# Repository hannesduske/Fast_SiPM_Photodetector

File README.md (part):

# Fast SiPM Photodetector

This photodetector is built around the fast output of the onsemi MicroFC-30035 silicon photomultiplier (SiPM).
It combines an adjustable sensor-bias supply, an integrated low-noise amplifier, and an analog temperature sensor for external temperature control.
The detector can measure nanosecond-scale events and achieves single-photon resolution.

<div align="center">
<table style="border: none;">
  <tr>
    <td style="text-align:center">
      <br>
    </td>
    <td style="text-align:center">
      <br>
    </td>
  </tr>
</table>
</div>

## Table of Contents

- [1. Technical Specification](#1-technical-specification)
  - [1.1 Key Features](#11-key-features)
  - [1.2 Design Specification](#12-design-specification)
  - [1.3 The MicroFC-30035 SiPM](#13-the-microfc-30035-sipm)
- [2. Circuit Design](#2-circuit-design)
  - [2.1 Overview](#21-overview)
  - [2.2 Input Protection](#22-input-protection)
  - [2.3 HV Power Supply](#23-hv-power-supply)
  - [2.4 LV Power Supply](#24-lv-power-supply)
  - [2.5 Photodetector](#25-photodetector)
  - [2.6 Amplifier](#26-amplifier)
  - [2.7 Temperature Sensor](#27-temperature-sensor)
- [3. PCB Layout](#3-pcb-layout)
  - [3.1 Physical Dimensions](#31-physical-dimensions)
  - [3.2 Peripheral Components](#32-peripheral-components)
  - [3.3 Assembled Detector Boards](#33-assembled-detector-boards)
- [4. Detector Performance](#4-detector-performance)
  - [4.1 Output Noise Performance](#41-output-noise-performance)
  - [4.2 Thermal Performance, Active Cooling and Dark Count](#42-thermal-performance-active-cooling-and-dark-count)
  - [4.3 Single Photon Detection](#43-single-photon-detection)
  - [4.4 Observing Nanosecond Light Pulses](#44-observing-nanosecond-light-pulses)
- [5. References](#5-references)
  - [5.1 Datasheets of Main Components](#51-datasheets-of-main-components)
  - [5.2 Reference Documents](#52-reference-documents)
  - [5.3 Design Tools](#53-design-tools)

## 1. Technical Specification

### 1.1 Key Features

This detector board is built around the [MicroFC-30035](https://www.onsemi.com/pub/Collateral/MICROC-SERIES-D.PDF) SiPM and uses its fast output for readout.
The fast output is amplified by a [GALI-S66+](https://www.minicircuits.com/pdfs/GALI-S66+.pdf) RF amplifier.
The SiPM bias voltage is generated by an integrated [LT8365](https://www.analog.com/media/en/technical-documentation/data-sheets/lt8365.pdf) boost converter followed by an adjustable low-noise LDO and can be adjusted from $23.8\ \mathrm{V}$ to $29.1\ \mathrm{V}$.
Separate high-voltage and low-voltage power rails are created on board from a single input voltage.

An [MCP9700A](https://ww1.microchip.com/downloads/en/devicedoc/20001942g.pdf) analog temperature sensor is also included on the board to enable external temperature control.

### 1.2 Design Specification

<div align="center">

| Parameter | Value |
|-|-|
| Input Voltage | $7.5\ \mathrm{V}$ to $24\ \mathrm{V}$ |
| SiPM | onsemi MicroFC-30035 |
| SiPM Bias Adjustment | $23.8\ \mathrm{V}$ to $29.1\ \mathrm{V}$ |
| Amplifier | GALI-S66+ |
| Fast-Output Amplification | $+20.3\ \mathrm{dB}$ @ $1\ \mathrm{GHz}$ (typ.) |
| Amplifier Output | Voltage readout, $50\ \Omega$ matched |
| Temperature Sensor | MCP9700A with analog output |
| Input Protection | Reverse voltage protection <br> Short-circuit protection |

</div>

> ℹ️ The lower input voltage limit is set by the undervoltage shutdown of the high-voltage supply. Refer to [2.3](#23-hv-power-supply).

> ℹ️ The MicroFC-30035 datasheet specifies a breakdown voltage of $24.2\ \mathrm{V}$ to $24.7\ \mathrm{V}$ and a recommended overvoltage of $1\ \mathrm{V}$ to $5\ \mathrm{V}$.
> The upper bias limit of $29.1\ \mathrm{V}$ corresponds to an overvoltage of $4.4\ \mathrm{V}$ to $4.9\ \mathrm{V}$.
> The lower bias limit of $23.8\ \mathrm{V}$ is below the breakdown voltage.

### 1.3 The MicroFC-30035 SiPM

The MicroFC-30035 was chosen for this project because of its unique fast output.

The fast output of the MicroFC-30035 has a rise time of $600\ \mathrm{ps}$ and is well suited for timing experiments and for observing fast transients.
The electronic readout and amplification of the fast output are also very simple.
Because it is a direct voltage output, it can be amplified with standard wideband RF amplifiers.

The MicroFC-30035 is sensitive to blue light and has its peak sensitivity at $420\ \mathrm{nm}$.

<div align="center">
  <br>
  <p>Photon Detection Efficiency (PDE) of the MicroFC-30035 (<a href="https://www.onsemi.com/pub/Collateral/MICROC-SERIES-D.PDF">Datasheet p. 7</a>)</p>
</div>

## 2. Circuit Design

### 2.1 Overview

<div align="center">
  <br>
</div>

The complete schematic is available [here](01_Docs/02_Schematic/sipm_photo_detector_v0_2.pdf) as a PDF.

The MicroFC-30035 is the main component of this detector board, and the entire circuit is designed to maximize its performance through:
- heavy filtering on the SiPM and amplifier supply rails
- $50\ \Omega$ matched transmission lines and high-frequency RF components
- EMI shielding

### 2.2 Input Protection

<div align="center">
  <br>
</div>

The detector is protected against reverse input voltages through MOSFET $\mathrm{Q1}$.
Additionally, the input stage includes the SMD fuse $\mathrm{F1}$ for short-circuit protection.
The detector can be physically turned on and off by switch $\mathrm{SW1}$.

There are no power indicator LEDs on the board to avoid interference with the sensor.

### 2.3 HV Power Supply

<div align="center">
  <br>
</div>

The high-voltage rail is exclusively used to supply the SiPM bias voltage.
It is generated with the LT8365 boost converter $\mathrm{IC1}$ and is set to $30.4\ \mathrm{V}$ by the feedback resistors $\mathrm{R5}$ and $\mathrm{R6}$.
The converter input is filtered by the ferrite bead $\mathrm{FB1}$ and the surrounding capacitors.

The high-voltage regulator shuts down when the input voltage falls below $7.5\ \mathrm{V}$.
This undervoltage threshold is set by the enable network formed by $\mathrm{R7}$ and $\mathrm{R8}$.

### 2.4 LV Power Supply

<div align="center">
  <br>
</div>

The low-voltage supply uses the LMR51606 buck converter $\mathrm{IC2}$ to generate a fixed $6.6\ \mathrm{V}$ rail.
The output voltage is set by the feedback network formed by $\mathrm{R11}$ and $\mathrm{R12}$.
The converter input is filtered by the ferrite bead $\mathrm{FB3}$ and the surrounding capacitors.

The enable network formed by $\mathrm{R9}$ and $\mathrm{R10}$ monitors the high-voltage rail and turns the converter on at approximately $23.3\ \mathrm{V}$.
The low-voltage rail therefore only turns on once the high-voltage supply has stabilized.

The output voltage is set as high as possible for the minimum input voltage of $7.5\ \mathrm{V}$ to improve amplifier performance.

### 2.5 Photodetector

<div align="center">
  <br>
</div>

The HV supply rail is filtered with a capacitance multiplier stage that is built with the Darlington transistor $\mathrm{Q2}$ to minimize supply ripple from the LT8365 converter.
The filtered voltage is then reduced further with the adjustable low-noise LDO $\mathrm{IC4}$ to precisely set the SiPM bias voltage.
The bias voltage is continuously adjustable from $23.8\ \mathrm{V}$ to $29.1\ \mathrm{V}$ with the on-board potentiometer $\mathrm{RV1}$.

It is possible to override the on-board potentiometer with an external one for use cases where the detector is integrated into a larger assembly.
To keep the circuit simple, the external potentiometer is connected in parallel with $\mathrm{RV1}$.
Therefore, when using an external potentiometer, the on-board potentiometer must be set to its **highest resistance** to produce the **minimum bias voltage**.
The output voltage can then be adjusted with a high-resistance external potentiometer connected between `BIAS_ADJ` (CONN2 pin 1) and `GND` (CONN2 pin 2).
An external potentiometer with a resistance of at least $100\ \mathrm{k}\Omega$ is recommended to preserve the full voltage adjustment range.

> ℹ️ The MicroFC application note [AND9782-D](https://www.onsemi.com/pub/Collateral/AND9782-D.PDF) recommends using a negative bias on the anode, with the cathode at $0\ \mathrm{V}$, for the best fast-output timing performance of this SiPM.
> Currently, a positive supply rail is used, but the LT8365 can be configured to generate a negative voltage instead.
> In this case, the adjustable LDO would need to be replaced with a negative-voltage version.

### 2.6 Amplifier

<div align="center">
  <br>
</div>

The fast-output signal is amplified by the GALI-S66+ RF amplifier $\mathrm{U1}$.
This stage is critical to detector performance and is laid out as a dedicated high-frequency signal path with an optional shielding can.
The high-frequency path uses $50\ \Omega$ transmission lines and high-quality C0G/NP0 capacitors for improved performance.
The amplifier's bias tee uses two RF inductors of different sizes, $\mathrm{L3}$ and $\mathrm{L4}$, for good performance over a wide frequency range.

A second capacitance multiplier stage with the Darlington transistor $\mathrm{Q3}$, similar to the one in the SiPM bias supply, is used to filter the amplifier supply voltage.

### 2.7 Temperature Sensor

<div align="center">
  <br>
</div>

The local $3.3\ \mathrm{V}$ LDO $\mathrm{U2}$ powers the MCP9700A temperature sensor $\mathrm{U3}$ from the low-voltage rail.
The MCP9700A outputs an analog voltage that changes linearly with the sensor temperature.
The temperature sensor output is filtered with the small capacitor $\mathrm{C26}$ and protected by the series resistor $\mathrm{R18}$ to prevent damage in case the output pin is accidentally shorted.

> ℹ️ The [MCP9700A datasheet](https://ww1.microchip.com/downloads/en/devicedoc/20001942g.pdf) specifies a typical output voltage of $500\ \mathrm{mV}$ at $T_A=0\ \mathrm{^\circ C}$ and a temperature coefficient of $T_C=10\ \mathrm{mV/^\circ C}$.
> The sensor temperature can therefore be calculated as $T_A=(U_{out} - 0.5\ \mathrm{V}) \cdot 100 \frac{\mathrm{^\circ C}}{\mathrm{V}}$.
> Refer to the MCP9700A datasheet for more information on sensor readout and accuracy.

> ℹ️ The temperature sensor is provided as an auxiliary feature to support an external temperature controller.
> The detector board does not include the controller's power electronics for the following reasons:
> - A linear controller is recommended over a switching controller to protect the sensitive detector circuit from switching noise.
> - Linear controllers dissipate significant power and generate heat.
> - This heat must be kept away from the SiPM. Otherwise, it would counteract the active cooling.
>
> For these reasons, the temperature controller is to be implemented externally.

## 3. PCB Layout

### 3.1 Physical Dimensions

The V0.2 PCB measures $60\ \mathrm{mm} \times 40\ \mathrm{mm}$ and has an M3 hole pattern of $50\ \mathrm{mm} \times 30\ \mathrm{mm}$.

The PCB is laid out around the central MicroFC-30035.
Care has been taken to keep switching signals away from the sensor and amplifier, and a four-layer PCB stackup has been chosen for better EMI performance.
Additionally, the amplifier stage is designed to fit inside a $10\ \mathrm{mm} \times 15\ \mathrm{mm}$ clip-on metal shielding can.

The center of the bottom layer of the PCB is intentionally kept free of components and THT holes to allow a $40\ \mathrm{mm} \times 40\ \mathrm{mm}$ thermoelectric cooler to be mounted directly below the sensor.

<div align="center">
  <br>
</div>

### 3.2 Peripheral Components

Below is a functional description of the main peripheral components of the PCB.

<div align="center">
<br>

| Reference | Description |
|-|-|
| SW1   | On/off switch. Switches the input voltage. |
| POT1  | Bias voltage adjustment. |
| SMA1  | Amplified fast output of the SiPM ($50\ \Omega$). |
| CONN1 | DC input. $7.5\ \mathrm{V}$ to $24\ \mathrm{V}$. Pin order: `V`, `G`. Mating plug: [PTSM 0,5/ 2-P-2,5](https://www.phoenixcontact.com/en-de/products/pcb-connector-ptsm-05-2-p-25-1778832). |
| CONN2 | External bias override and analog temperature output, each with its own ground pin. Pin order: `B` (`BIAS_ADJ`), `G`, `T` (`TEMP_OUT`), `G`. Mating plug: [PTSM 0,5/ 4-P-2,5](https://www.phoenixcontact.com/en-de/products/pcb-connector-ptsm-05-4-p-25-1778858). |
| FUSE1 | 0603 SMD fuse ($3\ \mathrm{A}$) for short-circuit protection. |
</div>

> ℹ️ The connectors on the board are the PTSM 0,5/ 2-HH-2,5-SMD R32 (CONN1) and PTSM 0,5/ 4-HH-2,5-SMD R32 (CONN2) headers.

### 3.3 Assembled Detector Boards

The front and back of the assembled Fast SiPM Photodetector V0.2 PCB are shown below.
Two boards were assembled for performance testing.

<div align="center">
  <br>
  <p>Front and back sides of the assembled Fast SiPM Photodetector V0.2 PCB.</p>
</div>

## 4. Detector Performance

### 4.1 Output Noise Performance

With the SiPM bias set to $24\ \mathrm{V}$, the measured output noise is $87.0\ \mathrm{\mu V RMS}$ over a bandwidth of $250\ \mathrm{MHz}$.
The dense baseline noise floor, approximately $0.8\ \mathrm{mV}$ peak-to-peak, remains constant across the bias adjustment range and across the input voltage range.
The trace also shows spikes at the LT8365 boost converter's switching frequency, with an amplitude of approximately $1.5\ \mathrm{mV}$ peak-to-peak.
As the input voltage increases, the spike frequency decreases and the measured total noise is reduced.

The main issue with these spikes is that they interfere with single-photon detection at bias voltages below $27\ \mathrm{V}$ because their amplitude is similar to that of single-photon events.
At bias voltages above $27\ \mathrm{V}$, the noise spikes can be distinguished cleanly from real detection events.

<div align="center">
<table style="border-collapse: collapse; border: none;">
  <tr>
    <td style="border: none; text-align: center;">
      <br>
      <p>Output noise at a SiPM bias voltage of $24\ \mathrm{V}$. Measured RMS value: $87.0\ \mathrm{\mu V}$ at $250\ \mathrm{MHz}$ bandwidth.</p>
    </td>
    <td style="border: none; text-align: center;">
      <br>
      <p>Output-noise spikes (yellow) coincide with the LT8365 switching transitions (blue).</p>
    </td>
  </tr>
</table>
</div>

The LT8365 switching node has very fast transitions, exceeding $850\ \mathrm{mV/ns}$, which couple into the output signal.
None of the following measures effectively attenuated the spikes:
- Decoupling the SiPM with an additional small, $100\ \mathrm{pF}$ C0G 0402 capacitor
- Adding a grounded metal shielding can around the boost converter
- Adding small capacitors to the LT8365 switching node for damping
- Adding an RC snubber to the switching node

In these tests, adding capacitance increased the ringing and, depending on the value, also increased the spike amplitude.

The most promising way to reduce this interference is to slow the switching edges directly.
The LT8365 uses an integrated switch, so its transition speed cannot be adjusted.
A boost converter with an external switch may be a better choice for a future revision because its switching speed can be tuned to limit interference.
Alternatively, a specialized ultra-low-EMI converter such as the [LT8336](https://www.analog.com/en/products/lt8336.html) may also reduce emissions.

### 4.2 Thermal Performance, Active Cooling and Dark Count

#### Bias Voltage and Dark Count

The SiPM dark-count rate and dark current increase with temperature and overvoltage, as shown in the left-hand plot from the MicroFC datasheet.
The plot shows the dark current of the larger $6\ \mathrm{mm} \times 6\ \mathrm{mm}$ MicroFC-60035 sensor so the absolute values differ for the MicroFC-30035, but the trends are similar.

<div align="center">
<table style="border-collapse: collapse; border: none;">
  <tr>
    <td style="border: none; text-align: center;">
      <br>
      <p>Dark current versus voltage and temperature of the MicroFC-60035 (<a href="https://www.onsemi.com/pub/Collateral/MICROC-SERIES-D.PDF">Datasheet p. 8</a>)</p>
    </td>
    <td style="border: none; text-align: center;">
      <br>
      <p>Gain versus voltage of the MicroFC family (<a href="https://www.onsemi.com/pub/Collateral/MICROC-SERIES-D.PDF">Datasheet p. 8</a>)</p>
    </td>
  </tr>
</table>
</div>

The voltage and temperature dependence of dark-count rate poses an inherent challenge for high-sensitivity applications.
These require high gain, which is achieved by increasing the overvoltage of the SiPM, but this also increases the dark-count rate.
In practice, this makes thermal management important to keep the dark-count rate as low as possible.
This design addresses this through careful thermal layout and optional active temperature control.

#### Thermal Layout of the Detector PCB

The first iteration of the detector PCB had slots milled around the SiPM to thermally isolate it from the surrounding components.
This turned out to be a poor design choice because the SiPM itself generates more heat than any other component on the board.
The slots did not isolate the SiPM from heat generated by other components but prevented it from dissipating its own heat, resulting in a higher sensor temperature.
In the second iteration, the slots were removed and replaced with a copper pour around the SiPM, with many vias connecting it thermally to the copper planes on the three lower PCB layers.

The thermal images below show the improved thermal layout of V0.2 compared to V0.1.
At the same bias voltage and after the same operating time, the sensor hotspot reading decreased by $5.9\ \mathrm{^\circ C}$.
Both detectors were set to a bias voltage of $25.1\ \mathrm{V}$, and no external heat sink or cooler was attached to the bottom of either PCB.

<div align="center">
<table style="border-collapse: collapse; border: none;">
  <tr>
    <td style="border: none; text-align: center;">
      <br>
      <p>PCB V0.1: 39.7 °C</p>
    </td>
    <td style="border: none; text-align: center;">
      <br>
      <p>PCB V0.2: 33.8 °C</p>
    </td>
  </tr>
</table>
</div>

The following thermal images of the second PCB version were taken 1 second, 30 seconds, 1 minute and 5 minutes after power-on.
They show the SiPM as the main local heat source and the improved thermal coupling between the sensor and the PCB, which helps spread the heat.
The detector was operated at a constant bias voltage of $25.1\ \mathrm{V}$, with no external heat sink or cooler attached to the bottom of the PCB.

<div align="center">
<table style="border-collapse: collapse; border: none;">
  <tr>
    <td style="border: none; text-align: center;">
      <br>
      <p>1 second after power-on</p>
    </td>
    <td style="border: none; text-align: center;">
      <br>
      <p>30 seconds after power-on</p>
    </td>
  </tr>
  <tr>
    <td style="border: none; text-align: center;">
      <br>
      <p>1 minute after power-on</p>
    </td>
    <td style="border: none; text-align: center;">
      <br>
      <p>5 minutes after power-on</p>
    </td>
  </tr>
</table>
</div>

#### Active Cooling and Dark Count

The thermal layout reduces heat build-up on the PCB, while active cooling offers a way to lower the SiPM temperature further.
This test evaluates the active-cooling concept and demonstrates how much it can improve detector performance by reducing the dark-count rate.
A V0.2 detector was mounted on a Peltier element coupled to a heatsink.
The images below show the assembly and its temperature distribution during operation.
The heatsink on the hot side of the Peltier element is crucial for cooling the detector board below ambient temperature.

<div align="center">
<table style="border-collapse: collapse; border: none;">
  <tr>
    <td style="border: none; text-align: center;">
      <br>
      <p>V0.2 detector mounted on a Peltier element and heatsink</p>
    </td>
    <td style="border: none; text-align: center;">
      <br>
      <p>Thermal image of the detector during active cooling</p>
    </td>
  </tr>
</table>
</div>

Starting at room temperature, the Peltier cooler was used to gradually lower the detector temperature while the dark-count rate was measured at bias voltages of $27\ \mathrm{V}$, $28\ \mathrm{V}$ and $29\ \mathrm{V}$.
For each plotted data point, the oscilloscope's pulse-counting function averaged the pulse counts across 100 consecutive $200\ \mathrm{\mu s}$ measurement intervals.
The temperature shown in the plot is measured by the on-board MCP9700A sensor.
Because of the thermal gradient between the PCB and the SiPM, this reading is somewhat lower than the actual SiPM temperature.

As the temperature decreased from $23\ \mathrm{^\circ C}$ to $9\ \mathrm{^\circ C}$, the dark-count rate fell by about $64\\%$ at a bias voltage of $27\ \mathrm{V}$, $64\\%$ at $28\ \mathrm{V}$, and $61\\%$ at $29\ \mathrm{V}$.
The reduction is substantial across all three bias settings, with the higher-bias measurements consistently showing a higher dark-count rate.

<div align="center">
  <br>
  <p>Measured SiPM dark-count rate versus temperature for three bias voltages.</p>
</div>

### 4.3 Single Photon Detection

The MicroFC-30035 produces distinct voltage pulses in response to individual photon events.
With the on-board amplifier, these pulses can be observed directly on any sufficiently fast oscilloscope.
The oscilloscope traces below show the pulses at two time scales.
The detailed view shows their pulse shapes, while the wider view captures multiple events over time.

The pulses have different discrete amplitudes, corresponding to different numbers of SiPM microcells firing in an event.
Single-cell events are most common, but the wider trace also shows pulses from events in which two or four cells fired.
This behavior is described in the onsemi [AND9770-D application note](https://www.onsemi.com/pub/Collateral/AND9770-D.PDF).

<div align="center">
<table style="border-collapse: collapse; border: none;">
    <tr>
        <td style="border: none; text-align: center;">
            <br>
            <p>SiPM output showing multiple photon events at a bias voltage of $29\ \mathrm{V}$.</p>
        </td>
        <td style="border: none; text-align: center;">
            <br>
            <p>Detailed view of individual photon pulses at a bias voltage of $29\ \mathrm{V}$.</p>
        </td>
    </tr>
</table>
</div>

The plot below shows the measured single-photon pulse amplitude versus SiPM bias voltage.
Across the measured range, the amplitude increases linearly from $1.0\ \mathrm{mV}$ at $26\ \mathrm{V}$ to $3.1\ \mathrm{mV}$ at $29\ \mathrm{V}$.

<div align="center">
  <br>
  <p>Measured single-photon signal amplitude versus SiPM bias voltage.</p>
</div>

### 4.4 Observing Nanosecond Light Pulses

The unique fast output of the MicroFC series makes this detector perfectly suited for observing nanosecond-scale light pulses.
As an example, the light responses of a generic blue LED and an ams OSRAM PLPT9 450LC_E laser diode were measured while pulsing each source with [this Avalanche Laser Driver](https://github.com/hannesduske/Avalanche_Laser_Driver).

<div align="center">
  <br>
  <p>Experimental setup with an avalanche diode driver on the left, a stack of ND filters in the middle and the Fast SiPM Photodetector V0.2 on the right.</p>
</div>

> ℹ️ The SiPM detector is too sensitive to measure either of the tested light sources directly at the tested operating conditions.
> A stack of ND8, ND64 and ND1000 neutral-density filters, with a combined attenuation of $512000$, was placed between the source and the detector for these measurements.

In the figures below, the cyan trace is the drive-current pulse and the yellow trace is the SiPM output.
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
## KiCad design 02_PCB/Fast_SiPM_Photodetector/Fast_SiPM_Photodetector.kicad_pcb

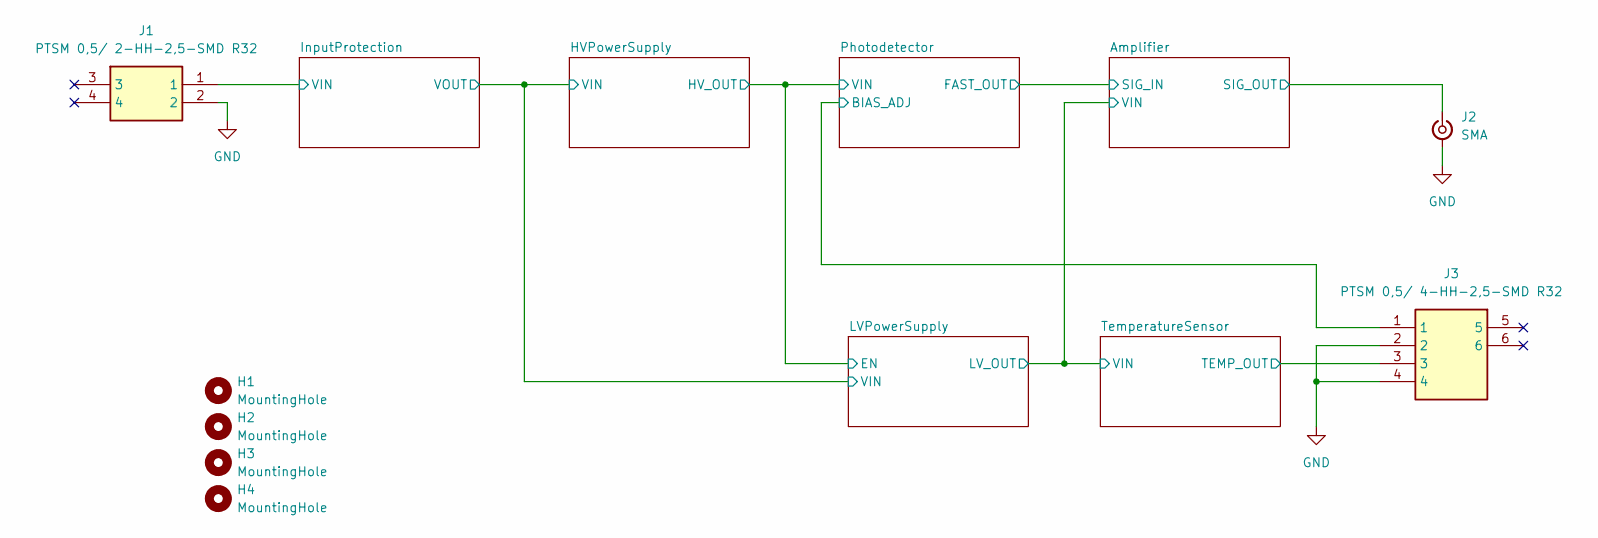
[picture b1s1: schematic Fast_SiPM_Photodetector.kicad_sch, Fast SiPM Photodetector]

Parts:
H1, H2, H3, H4: MountingHole; MountingHole_3.2mm_M3
J1: PTSM 0,5/ 2-HH-2,5-SMD R32; PTSM 0,5 2-HH-2,5-SMD R32; Mouser Part Number 651-1778764
J2: SMA; SMA_Samtec_SMA-J-P-H-ST-EM1_EdgeMount
J3: PTSM 0,5/ 4-HH-2,5-SMD R32; PTSM 0,5 4-HH-2,5-SMD R32; Mouser Part Number 651-1778780

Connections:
/Amplifier/SIG_OUT: J2.1 (In); also elsewhere on the board
/InputProtection/VIN: J1.1; also elsewhere on the board
/Photodetector/BIAS_ADJ: J3.1; also elsewhere on the board
/TemperatureSensor/TEMP_OUT: J3.3; also elsewhere on the board
GND: J1.2, J2.2 (Ext), J3.2, J3.4; also elsewhere on the board

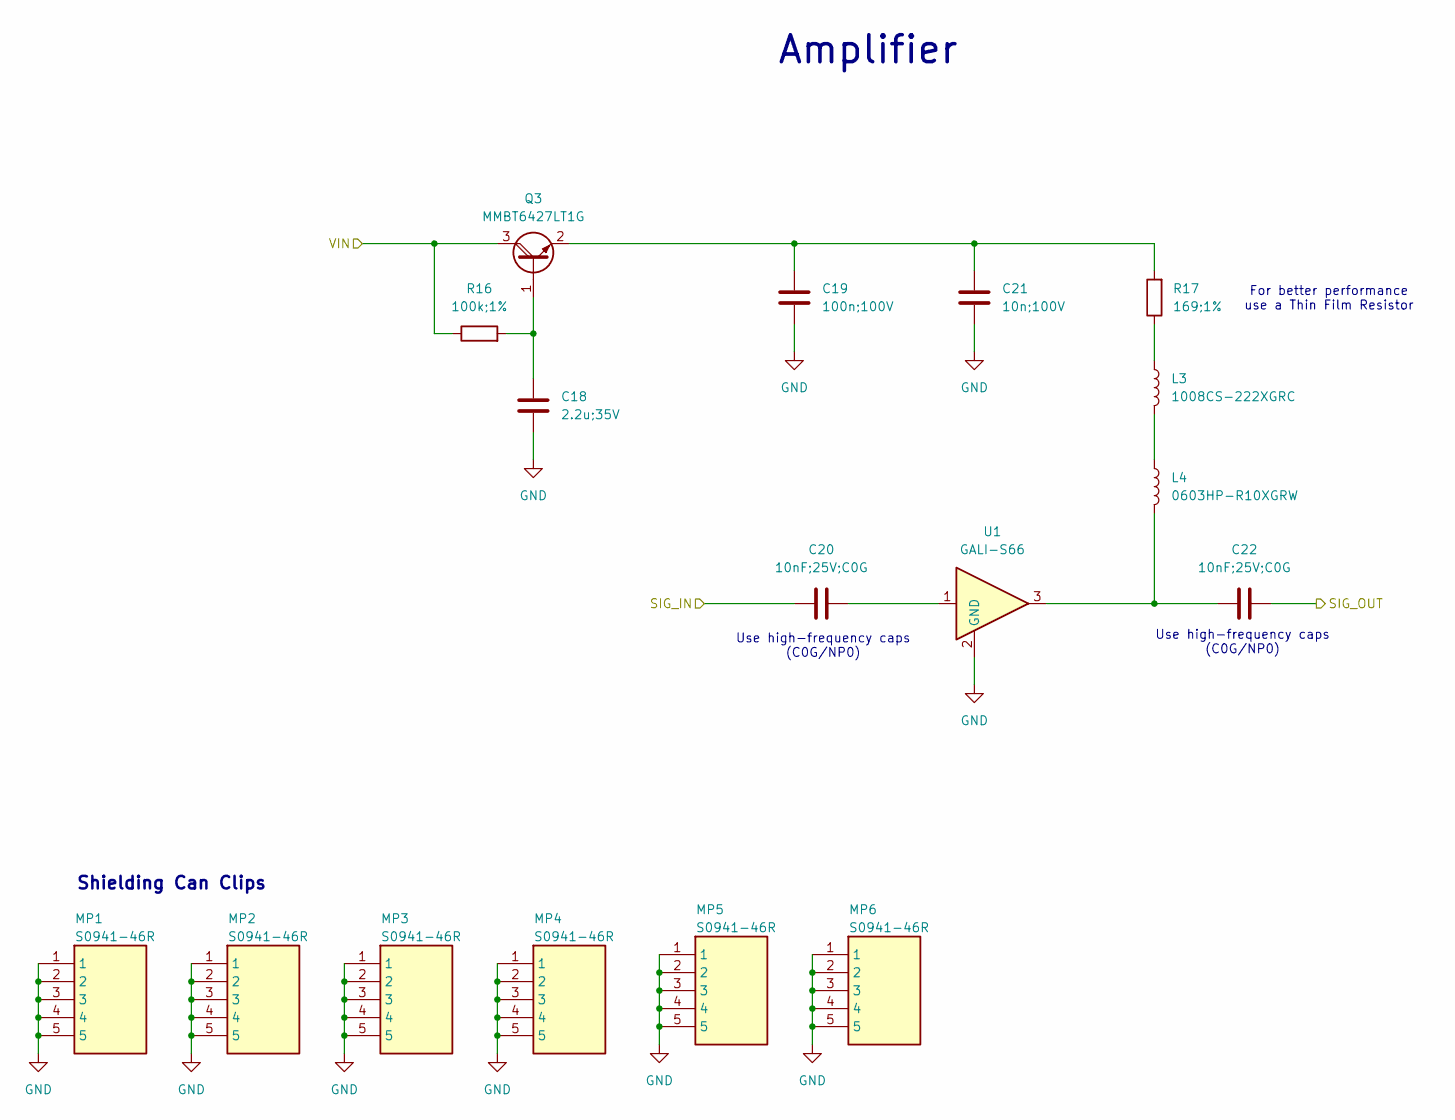
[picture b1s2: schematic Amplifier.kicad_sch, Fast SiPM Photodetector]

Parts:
C18: 2.2u;35V; C_0603_1608Metric
C19: 100n;100V; C_0603_1608Metric
C20, C22: 10nF;25V;C0G; C_0402_1005Metric
C21: 10n;100V; C_0603_1608Metric
L3: 1008CS-222XGRC; L_1008_2520Metric
L4: 0603HP-R10XGRW; L_0603_1608Metric
MP1, MP2, MP3, MP4, MP5, MP6: S0941-46R; S094146R; Mouser Part Number 855-S0941-46R
Q3: MMBT6427LT1G; SOT-23
R16: 100k;1%; R_0603_1608Metric
R17: 169;1%; R_0805_2012Metric
U1: GALI-S66; SOT-89-3

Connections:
/Amplifier/SIG_IN: C20.1; also elsewhere on the board
/Amplifier/SIG_OUT: C22.2; also elsewhere on the board
/LVPowerSupply/LV_OUT: Q3.3 (C), R16.1; also elsewhere on the board
GND: C18.2, C19.2, C21.2, MP1.1, MP1.2, MP1.3, MP1.4, MP1.5, MP2.1, MP2.2, MP2.3, MP2.4, MP2.5, MP3.1, MP3.2, MP3.3, MP3.4, MP3.5, MP4.1, MP4.2, MP4.3, MP4.4, MP4.5, MP5.1, MP5.2, MP5.3, MP5.4, MP5.5, MP6.1, MP6.2, MP6.3, MP6.4, MP6.5, U1.2 (GND_2); also elsewhere on the board
unnamed: C20.2, U1.1
unnamed: C22.1, L4.2, U1.3
unnamed: L3.1, R17.1
unnamed: L3.2, L4.1
unnamed: C18.1, Q3.1 (B), R16.2
unnamed: C19.1, C21.1, Q3.2 (E), R17.2

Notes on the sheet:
Use high-frequency caps (C0G/NP0)
Shielding Can Clips
For better performance use a Thin Film Resistor
Amplifier

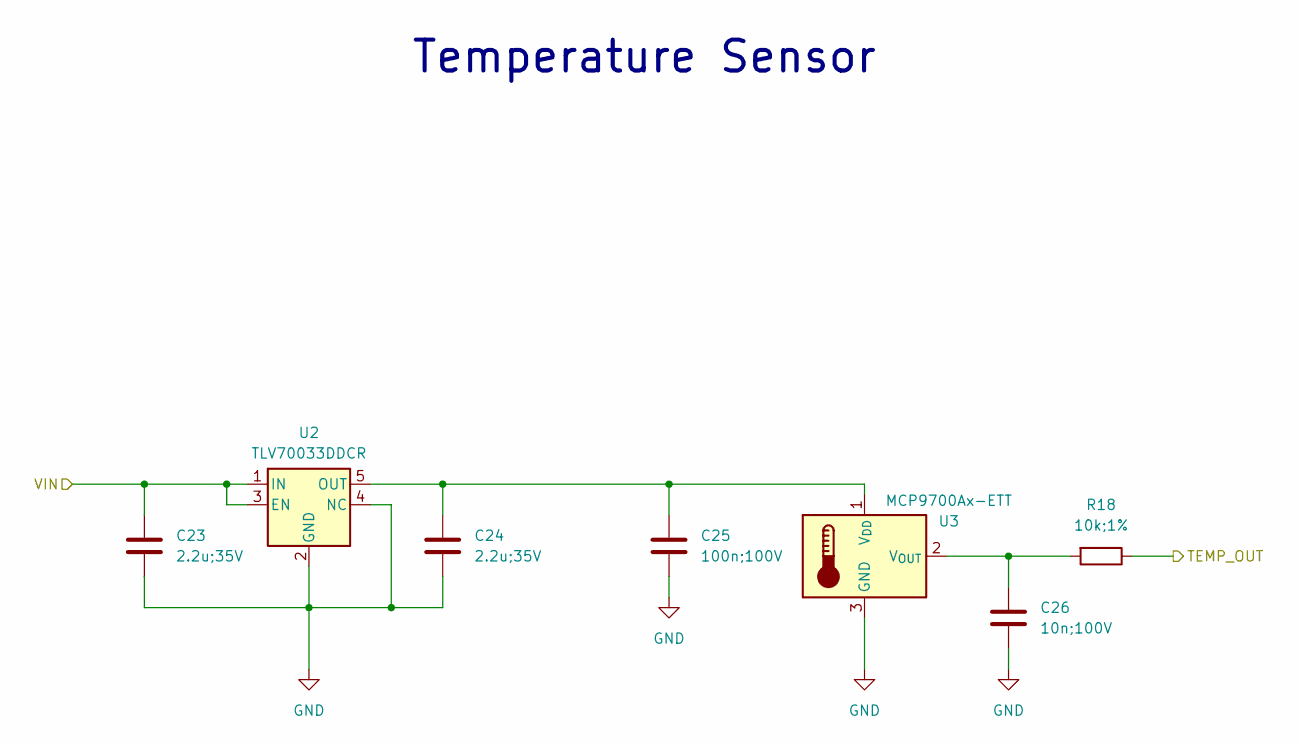
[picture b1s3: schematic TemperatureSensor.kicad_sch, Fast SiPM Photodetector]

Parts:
C23, C24: 2.2u;35V; C_0603_1608Metric
C25: 100n;100V; C_0603_1608Metric
C26: 10n;100V; C_0603_1608Metric
R18: 10k;1%; R_0603_1608Metric
U2: TLV70033DDCR; SOT-23-5
U3: MCP9700Ax-ETT; SOT-23

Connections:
/LVPowerSupply/LV_OUT: C23.1, U2.1 (IN), U2.3 (EN); also elsewhere on the board
/TemperatureSensor/TEMP_OUT: R18.1; also elsewhere on the board
GND: C23.2, C24.2, C25.2, C26.2, U2.2 (GND), U2.4 (NC), U3.3 (GND); also elsewhere on the board
unnamed: C24.1, C25.1, U2.5 (OUT), U3.1 (V_{DD})
unnamed: C26.1, R18.2, U3.2 (V_{OUT})

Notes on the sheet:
Temperature Sensor

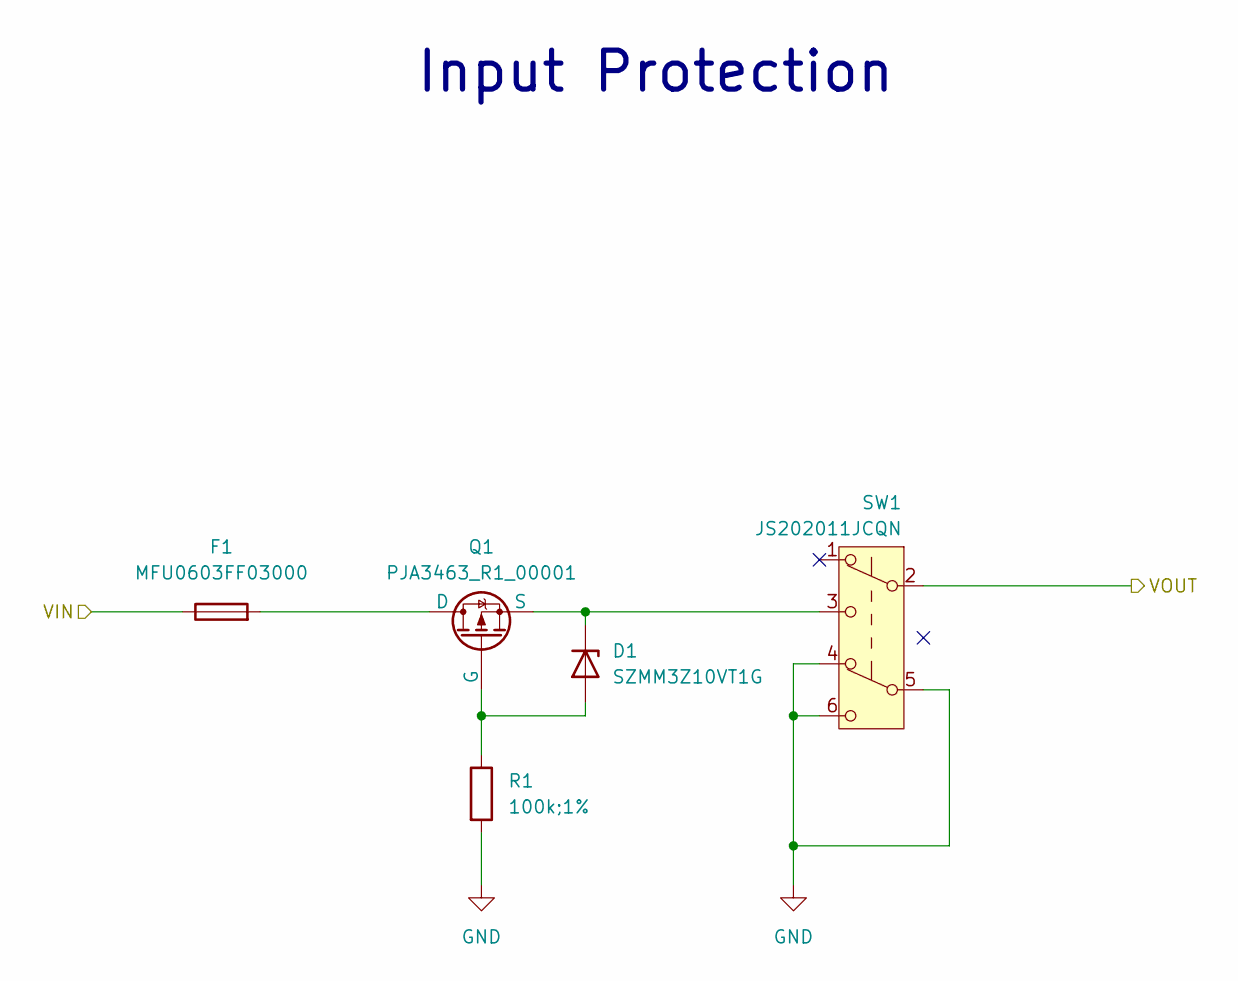
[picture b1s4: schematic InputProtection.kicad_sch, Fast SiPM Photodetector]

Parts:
D1: SZMM3Z10VT1G; D_SOD-323
F1: MFU0603FF03000; Fuse_0603_1608Metric
Q1: PJA3463_R1_00001; SOT-23
R1: 100k;1%; R_0603_1608Metric
SW1: JS202011JCQN; SW_DPDT_CK_JS202011JCQN

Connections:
/HVPowerSupply/VIN: SW1.2 (B); also elsewhere on the board
/InputProtection/VIN: F1.1; also elsewhere on the board
GND: R1.2, SW1.4 (A), SW1.5 (B), SW1.6 (C); also elsewhere on the board
unnamed: D1.2 (A), Q1.1 (G), R1.1
unnamed: D1.1 (K), Q1.2 (S), SW1.3 (C)
unnamed: F1.2, Q1.3 (D)

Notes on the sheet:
Input Protection

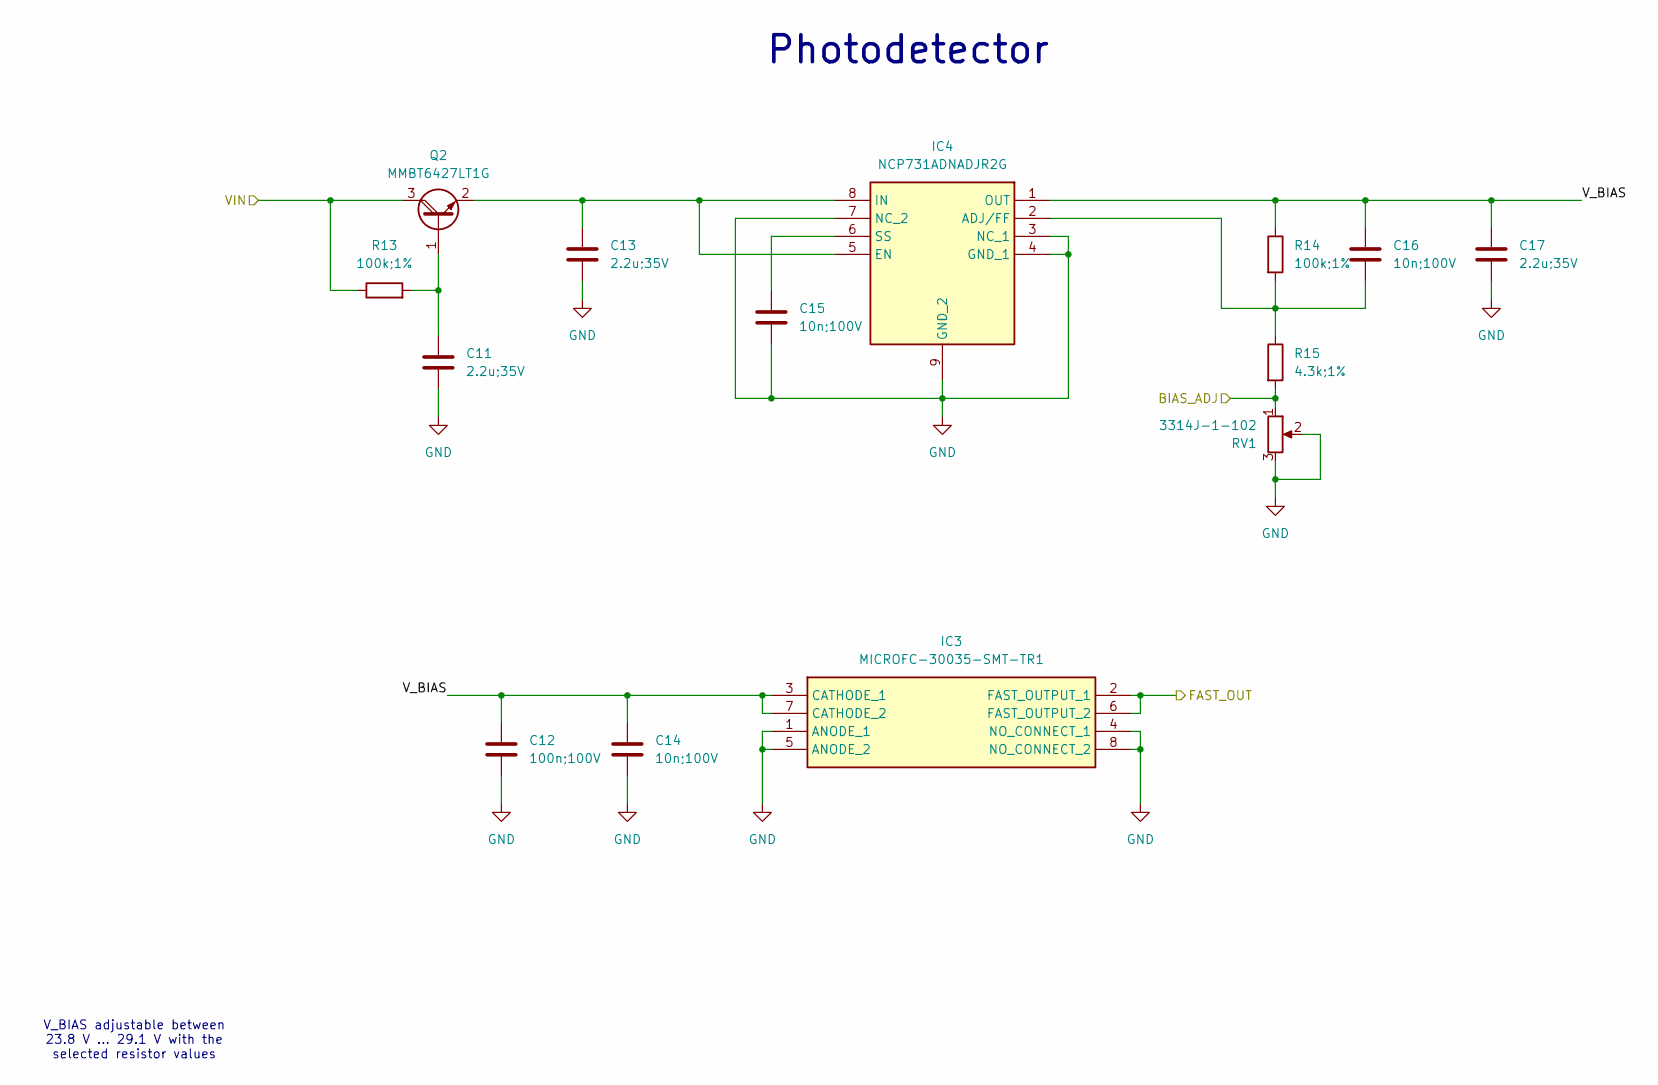
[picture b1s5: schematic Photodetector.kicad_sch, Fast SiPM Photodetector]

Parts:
C11, C13, C17: 2.2u;35V; C_0603_1608Metric
C12: 100n;100V; C_0603_1608Metric
C14, C15, C16: 10n;100V; C_0603_1608Metric
IC3: MICROFC-30035-SMT-TR1; MICROFC30035SMTTR1; Manufacturer_Part_Number MICROFC-30035-SMT-TR1; Mouser Part Number 863-MFC30035SMTTR1
IC4: NCP731ADNADJR2G; SOP65P488X110-9N; Mouser Part Number 863-NCP731ADNADJR2G
Q2: MMBT6427LT1G; SOT-23
R13, R14: 100k;1%; R_0603_1608Metric
R15: 4.3k;1%; R_0603_1608Metric
RV1: 3314J-1-102; Potentiometer_Bourns_3214J_Horizontal

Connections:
/Amplifier/SIG_IN: IC3.2 (FAST_OUTPUT_1), IC3.6 (FAST_OUTPUT_2); also elsewhere on the board
/HVPowerSupply/HV_OUT: Q2.3 (C), R13.1; also elsewhere on the board
/Photodetector/BIAS_ADJ: R15.2, RV1.1; also elsewhere on the board
/Photodetector/V_BIAS: C12.1, C14.1, C16.1, C17.1, IC3.3 (CATHODE_1), IC3.7 (CATHODE_2), IC4.1 (OUT), R14.1
GND: C11.2, C12.2, C13.2, C14.2, C15.2, C17.2, IC3.1 (ANODE_1), IC3.4 (NO_CONNECT_1), IC3.5 (ANODE_2), IC3.8 (NO_CONNECT_2), IC4.3 (NC_1), IC4.4 (GND_1), IC4.7 (NC_2), IC4.9 (GND_2), RV1.2, RV1.3; also elsewhere on the board
unnamed: C16.2, IC4.2 (ADJ/FF), R14.2, R15.1
unnamed: C13.1, IC4.5 (EN), IC4.8 (IN), Q2.2 (E)
unnamed: C15.1, IC4.6 (SS)
unnamed: C11.1, Q2.1 (B), R13.2

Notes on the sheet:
V_BIAS adjustable between 23.8 V ... 29.1 V with the selected resistor values
Photodetector

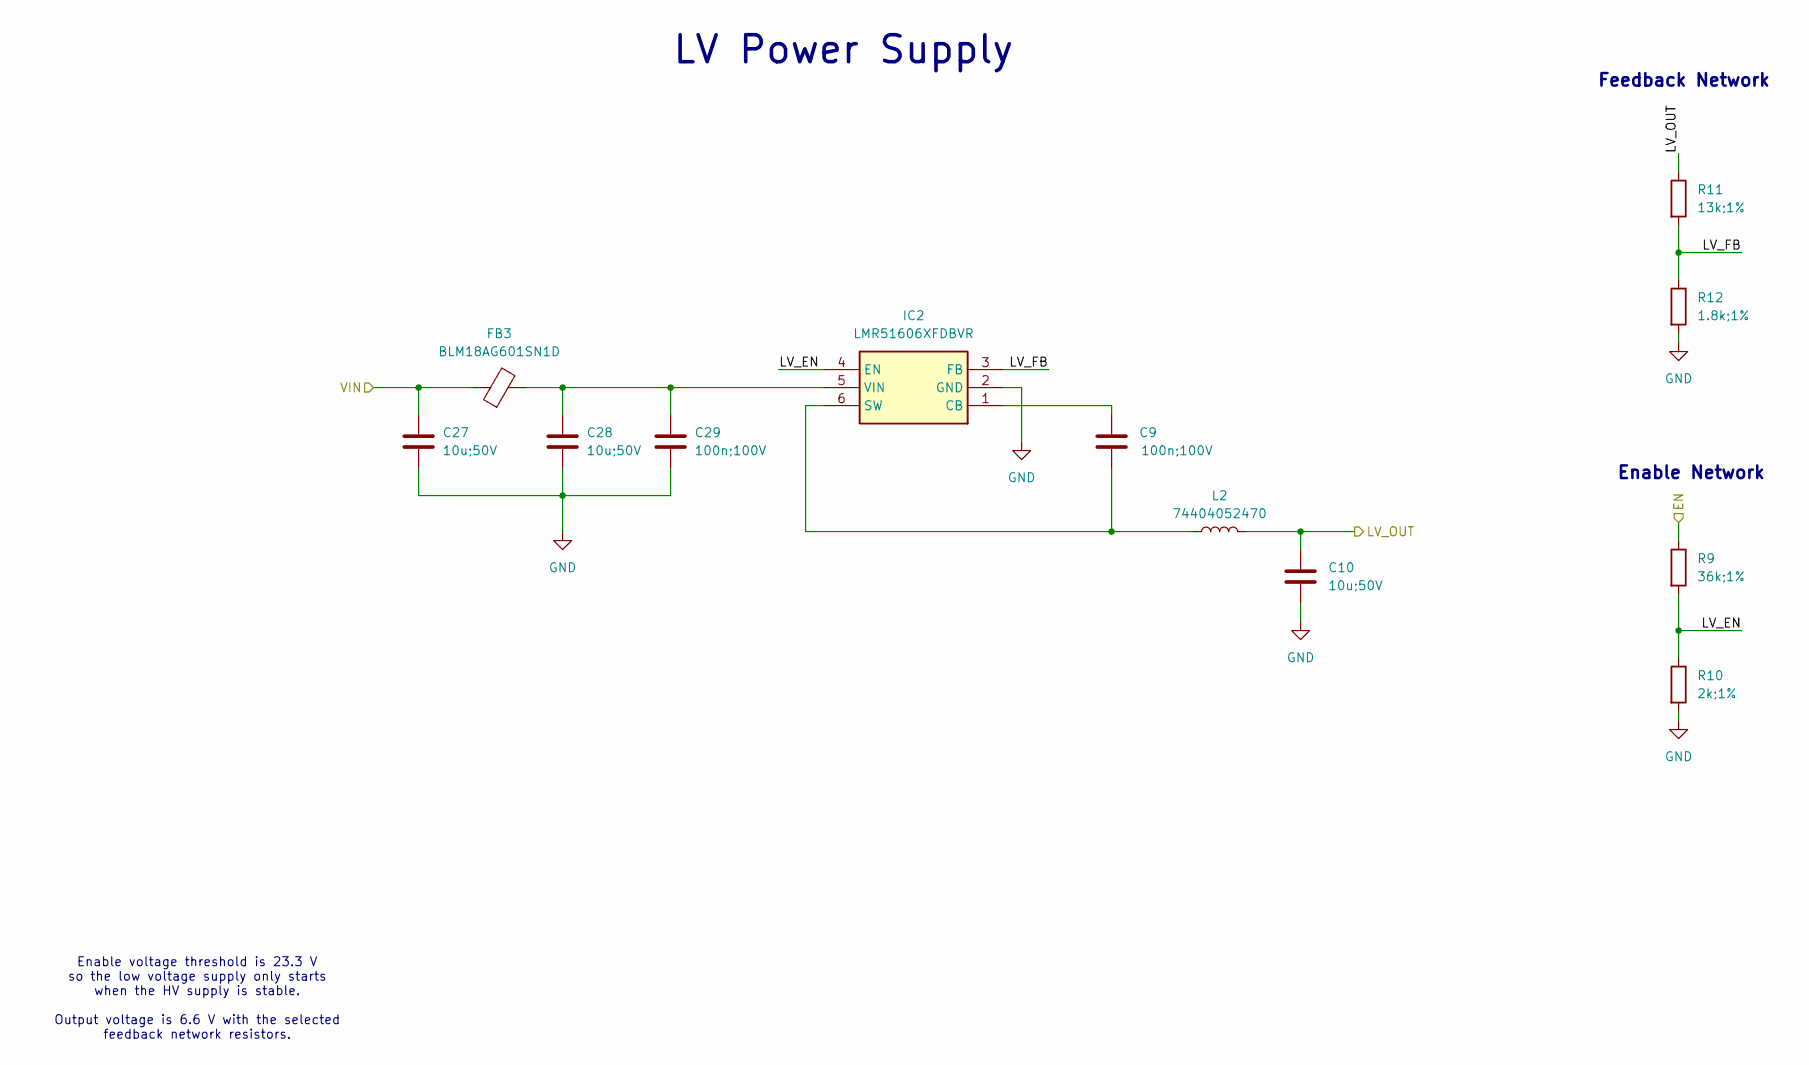
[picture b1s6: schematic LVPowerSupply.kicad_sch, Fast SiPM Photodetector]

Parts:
C9, C29: 100n;100V; C_0603_1608Metric
C10, C27, C28: 10u;50V; C_1206_3216Metric
FB3: BLM18AG601SN1D; L_0603_1608Metric
IC2: LMR51606XFDBVR; SOT95P280X145-6N; Mouser Part Number 595-LMR51606XDBVR
L2: 74404052470; L_Wuerth_MAPI-5020-Custom
R9: 36k;1%; R_0603_1608Metric
R10: 2k;1%; R_0603_1608Metric
R11: 13k;1%; R_0603_1608Metric
R12: 1.8k;1%; R_0603_1608Metric

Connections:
/HVPowerSupply/HV_OUT: R9.1; also elsewhere on the board
/HVPowerSupply/VIN: C27.2, FB3.1; also elsewhere on the board
/LVPowerSupply/LV_EN: IC2.4 (EN), R9.2, R10.1
/LVPowerSupply/LV_FB: IC2.3 (FB), R11.2, R12.1
/LVPowerSupply/LV_OUT: C10.1, L2.2, R11.1; also elsewhere on the board
GND: C10.2, C27.1, C28.1, C29.1, IC2.2 (GND), R10.2, R12.2; also elsewhere on the board
unnamed: C9.1, IC2.1 (CB)
unnamed: C9.2, IC2.6 (SW), L2.1
unnamed: C28.2, C29.2, FB3.2, IC2.5 (VIN)

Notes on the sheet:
Enable Network
Feedback Network
LV Power Supply
Enable voltage threshold is 23.3 V so the low voltage supply only starts when the HV supply is stable. Output voltage is 6.6 V with the selected feedback network resistors.

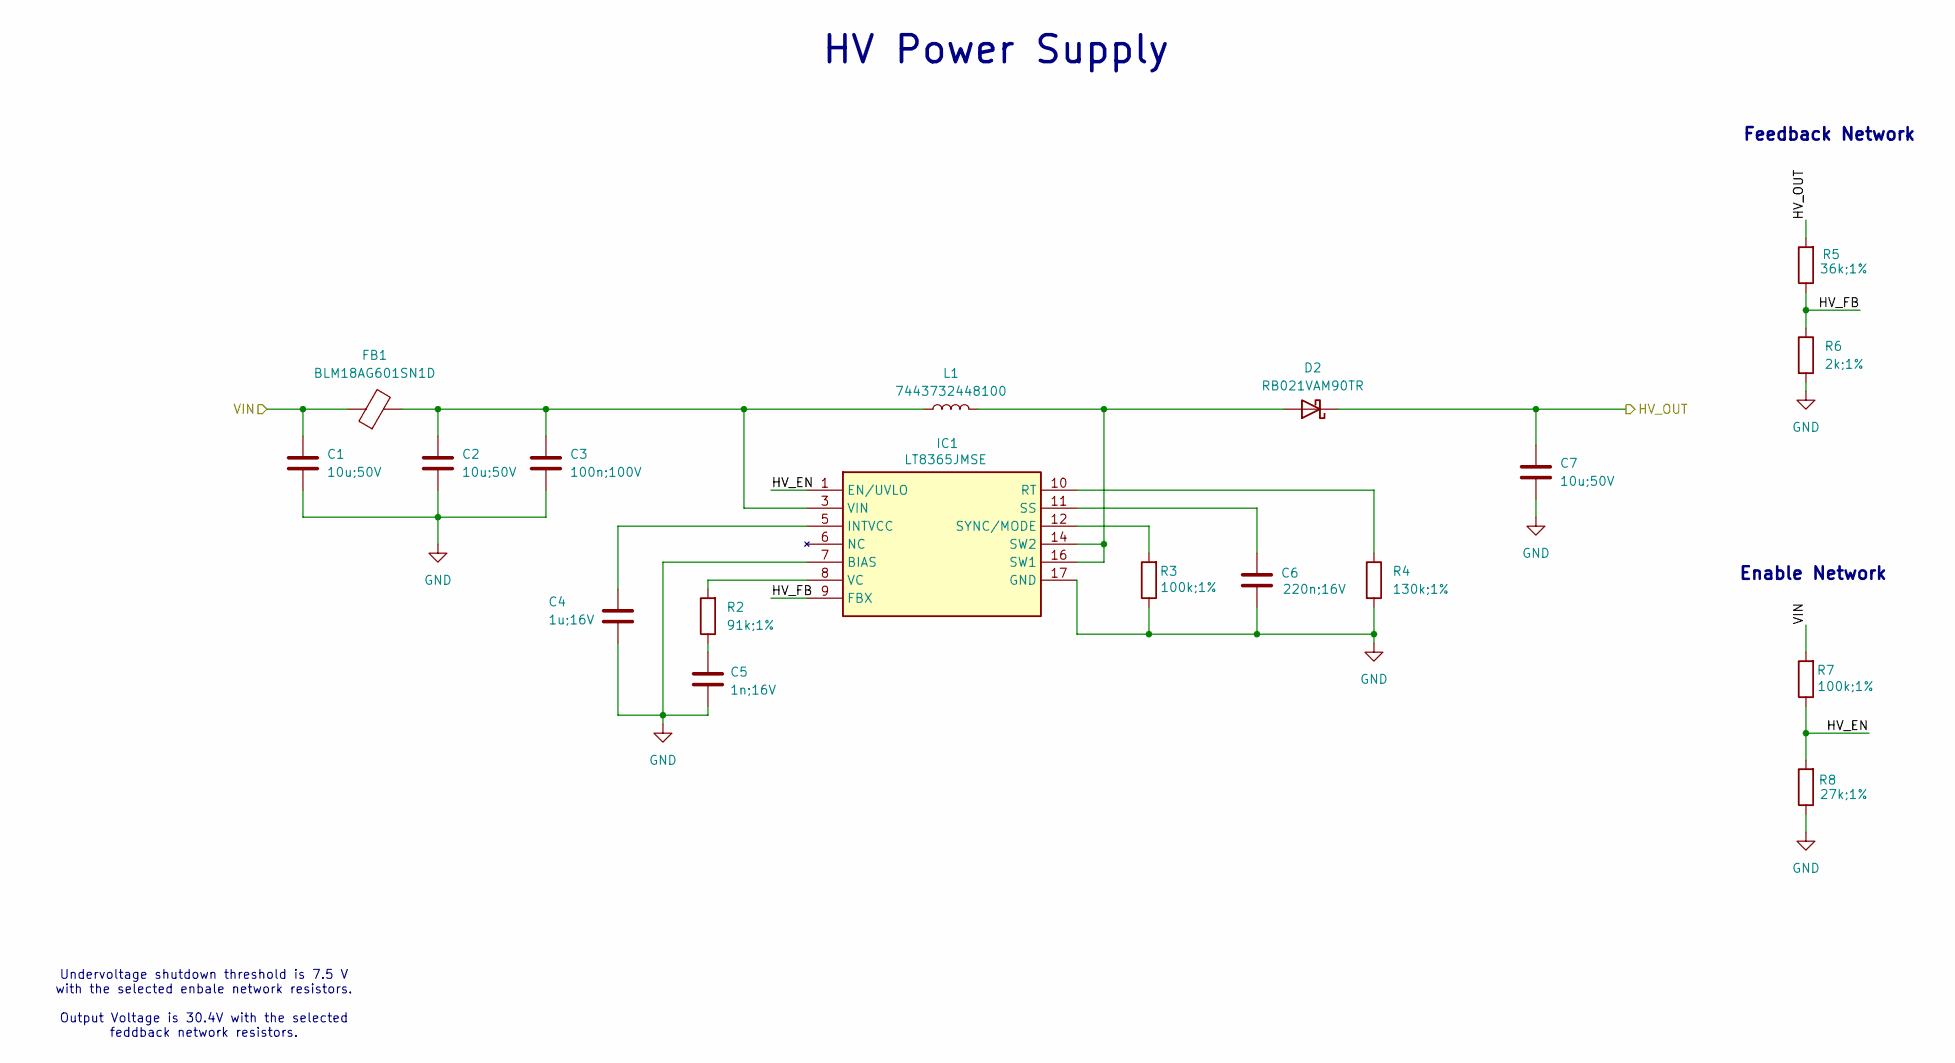
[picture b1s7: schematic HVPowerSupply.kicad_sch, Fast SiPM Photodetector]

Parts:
C1, C2, C7: 10u;50V; C_1206_3216Metric
C3: 100n;100V; C_0603_1608Metric
C4: 1u;16V; C_0603_1608Metric
C5: 1n;16V; C_0603_1608Metric
C6: 220n;16V; C_0603_1608Metric
D2: RB021VAM90TR; SMD115PBQTP
FB1: BLM18AG601SN1D; L_0603_1608Metric
IC1: LT8365JMSE; Analog_MSOP-12-16-1EP_3x4.039mm_P0.5mm_EP1.651x2.845mm; Mouser Part Number 584-LT8365JMSE
L1: 7443732448100; L_Wurth_WE-LQSH-4020
R2: 91k;1%; R_0603_1608Metric
R3, R7: 100k;1%; R_0603_1608Metric
R4: 130k;1%; R_0603_1608Metric
R5: 36k;1%; R_0603_1608Metric
R6: 2k;1%; R_0603_1608Metric
R8: 27k;1%; R_0603_1608Metric

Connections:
/HVPowerSupply/HV_EN: IC1.1 (EN/UVLO), R7.1, R8.2
/HVPowerSupply/HV_FB: IC1.9 (FBX), R5.1, R6.1
/HVPowerSupply/HV_OUT: C7.2, D2.1 (K), R5.2; also elsewhere on the board
/HVPowerSupply/VIN: C1.2, FB1.1, R7.2; also elsewhere on the board
GND: C1.1, C2.1, C3.1, C4.1, C5.1, C6.1, C7.1, IC1.7 (BIAS), IC1.17 (GND), R3.1, R4.2, R6.2, R8.1; also elsewhere on the board
unnamed: C5.2, R2.1
unnamed: D2.2 (A), IC1.14 (SW2), IC1.16 (SW1), L1.2
unnamed: C4.2, IC1.5 (INTVCC)
unnamed: IC1.10 (RT), R4.1
unnamed: C6.2, IC1.11 (SS)
unnamed: IC1.12 (SYNC/MODE), R3.2
unnamed: IC1.8 (VC), R2.2
unnamed: C2.2, C3.2, FB1.2, IC1.3 (VIN), L1.1

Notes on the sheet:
Undervoltage shutdown threshold is 7.5 V with the selected enbale network resistors. Output Voltage is 30.4V with the selected feddback network resistors.
Enable Network
HV Power Supply
Feedback Network

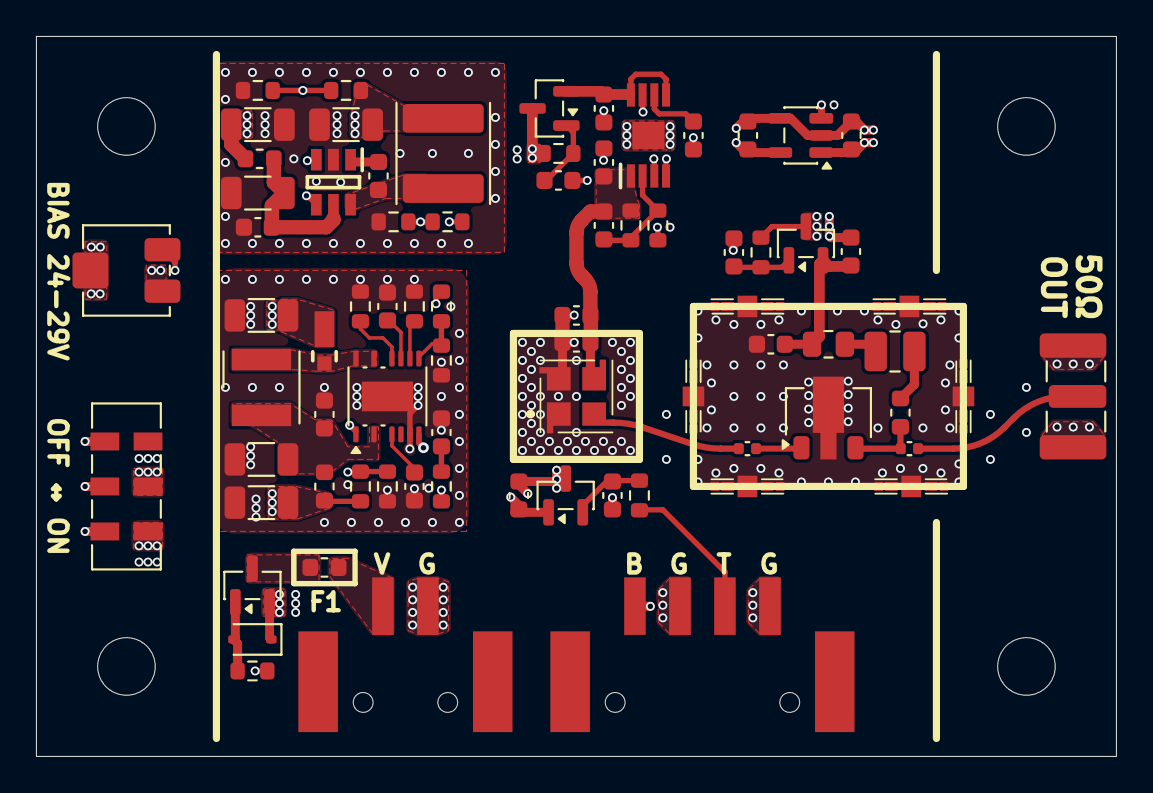
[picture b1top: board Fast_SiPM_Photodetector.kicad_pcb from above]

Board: 4 copper layers, 60.0 x 40.0 mm, 80 parts (0 on the bottom side), 40 nets.

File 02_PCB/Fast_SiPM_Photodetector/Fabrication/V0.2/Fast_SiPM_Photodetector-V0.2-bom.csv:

Designator,Footprint,Quantity,Value,LCSC Part #
"C1, C10, C2, C27, C28, C7",1206,6,10u;50V,
"C11, C13, C17, C18, C23, C24",0603,6,2.2u;35V,
"C12, C19, C25, C29, C3, C9",0603,6,100n;100V,
"C14, C15, C16, C21, C26",0603,5,10n;100V,
"C20, C22",0402,2,10nF;25V;C0G,
C4,0603,1,1u;16V,
C5,0603,1,1n;16V,
C6,0603,1,220n;16V,
D1,D_SOD-323,1,SZMM3Z10VT1G,
D2,SMD115PBQTP,1,RB021VAM90TR,
F1,0603,1,MFU0603FF03000,
"FB1, FB3",0603,2,BLM18AG601SN1D,
IC1,Analog_MSOP-12-16-1EP_3x4.039mm_P0.5mm_EP1.651x2.845mm,1,LT8365JMSE,
IC2,SOT95P280X145-6N,1,LMR51606XFDBVR,
IC3,MICROFC30035SMTTR1,1,MICROFC-30035-SMT-TR1,
IC4,SOP65P488X110-9N,1,NCP731ADNADJR2G,
J1,"PTSM 0,5 2-HH-2,5-SMD R32",1,"PTSM 0,5/ 2-HH-2,5-SMD R32",
J2,SMA_Samtec_SMA-J-P-H-ST-EM1_EdgeMount,1,SMA,
J3,"PTSM 0,5 4-HH-2,5-SMD R32",1,"PTSM 0,5/ 4-HH-2,5-SMD R32",
L1,L_Wurth_WE-LQSH-4020,1,7443732448100,
L2,L_Wuerth_MAPI-5020-Custom,1,74404052470,
L3,1008,1,1008CS-222XGRC,
L4,0603,1,0603HP-R10XGRW,
"MP1, MP2, MP3, MP4, MP5, MP6",S094146R,6,S0941-46R,
Q1,SOT-23,1,PJA3463_R1_00001,
"Q2, Q3",SOT-23,2,MMBT6427LT1G,
"R1, R13, R14, R16, R3, R7",0603,6,100k;1%,
"R10, R12, R6",0603,3,2k;1%,
R11,0603,1,13k;1%,
R15,0603,1,4.3k;1%,
R17,0805,1,169;1%,
R18,0603,1,10k;1%,
R2,0603,1,91k;1%,
R4,0603,1,130k;1%,
"R5, R9",0603,2,36k;1%,
R8,0603,1,27k;1%,
RV1,Potentiometer_Bourns_3214J_Horizontal,1,3314J-1-102,
SW1,SW_DPDT_CK_JS202011JCQN,1,JS202011JCQN,
U1,SOT-89-3,1,GALI-S66,
U2,SOT-23-5,1,TLV70033DDCR,
U3,SOT-23,1,MCP9700Ax-ETT,

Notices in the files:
README.md:
License:
This project is licensed under the CERN Open Hardware Licence Version 2 - Permissive ([CERN-OHL-P](https://ohwr.org/cern_ohl_p_v2.txt)).
Third-party datasheets, logos, and referenced documentation remain the property of their respective owners.
